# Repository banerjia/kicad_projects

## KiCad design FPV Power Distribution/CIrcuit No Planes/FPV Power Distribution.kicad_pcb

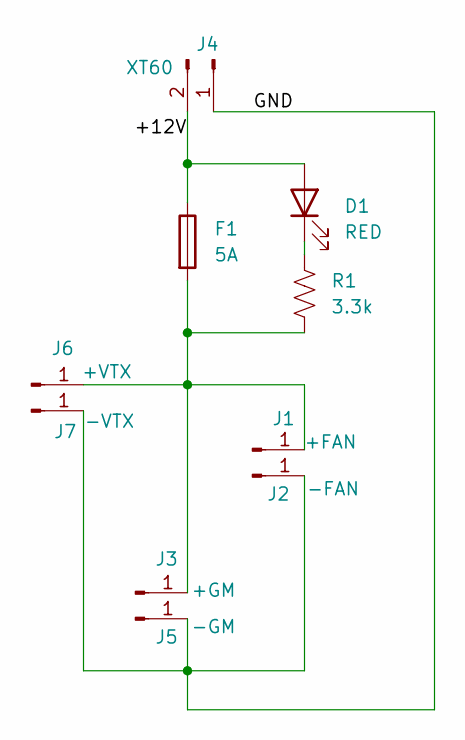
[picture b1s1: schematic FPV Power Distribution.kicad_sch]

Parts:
D1: RED; LED_0603_1608Metric_Pad1.05x0.95mm_HandSolder
F1: 5A; Fuseholder_Littelfuse_Nano2_154x
J1: +FAN; SolderWirePad_1x01_SMD_1x2mm
J2: -FAN; SolderWirePad_1x01_SMD_1x2mm
J3: +GM; SolderWirePad_1x01_SMD_1x2mm
J4: XT60; AMASS_XT60PW-M_1x02_P7.20mm_Horizontal
J5: -GM; SolderWirePad_1x01_SMD_1x2mm
J6: +VTX; SolderWirePad_1x01_SMD_1x2mm
J7: -VTX; SolderWirePad_1x01_SMD_1x2mm
R1: 3.3k; R_0603_1608Metric_Pad0.98x0.95mm_HandSolder

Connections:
/+12V: D1.2 (A), F1.1, J4.2
/GND: J2.1 (Pin_1_1), J4.1, J5.1 (Pin_1_1), J7.1 (Pin_1_1)
unnamed: D1.1 (K), R1.1
unnamed: F1.2, J1.1 (Pin_1_1), J3.1 (Pin_1_1), J6.1 (Pin_1_1), R1.2

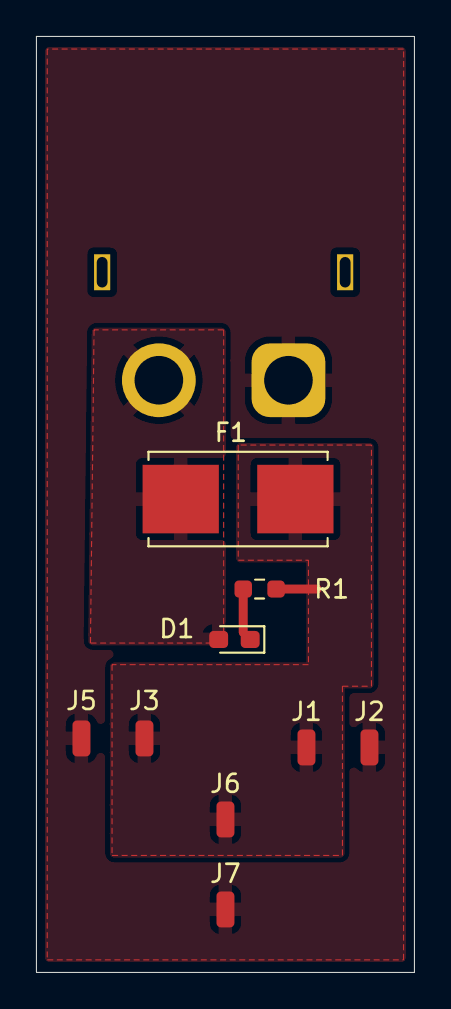
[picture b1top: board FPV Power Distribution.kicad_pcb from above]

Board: 2 copper layers, 21.0 x 52.0 mm, 10 parts (1 on the bottom side), 4 nets.
